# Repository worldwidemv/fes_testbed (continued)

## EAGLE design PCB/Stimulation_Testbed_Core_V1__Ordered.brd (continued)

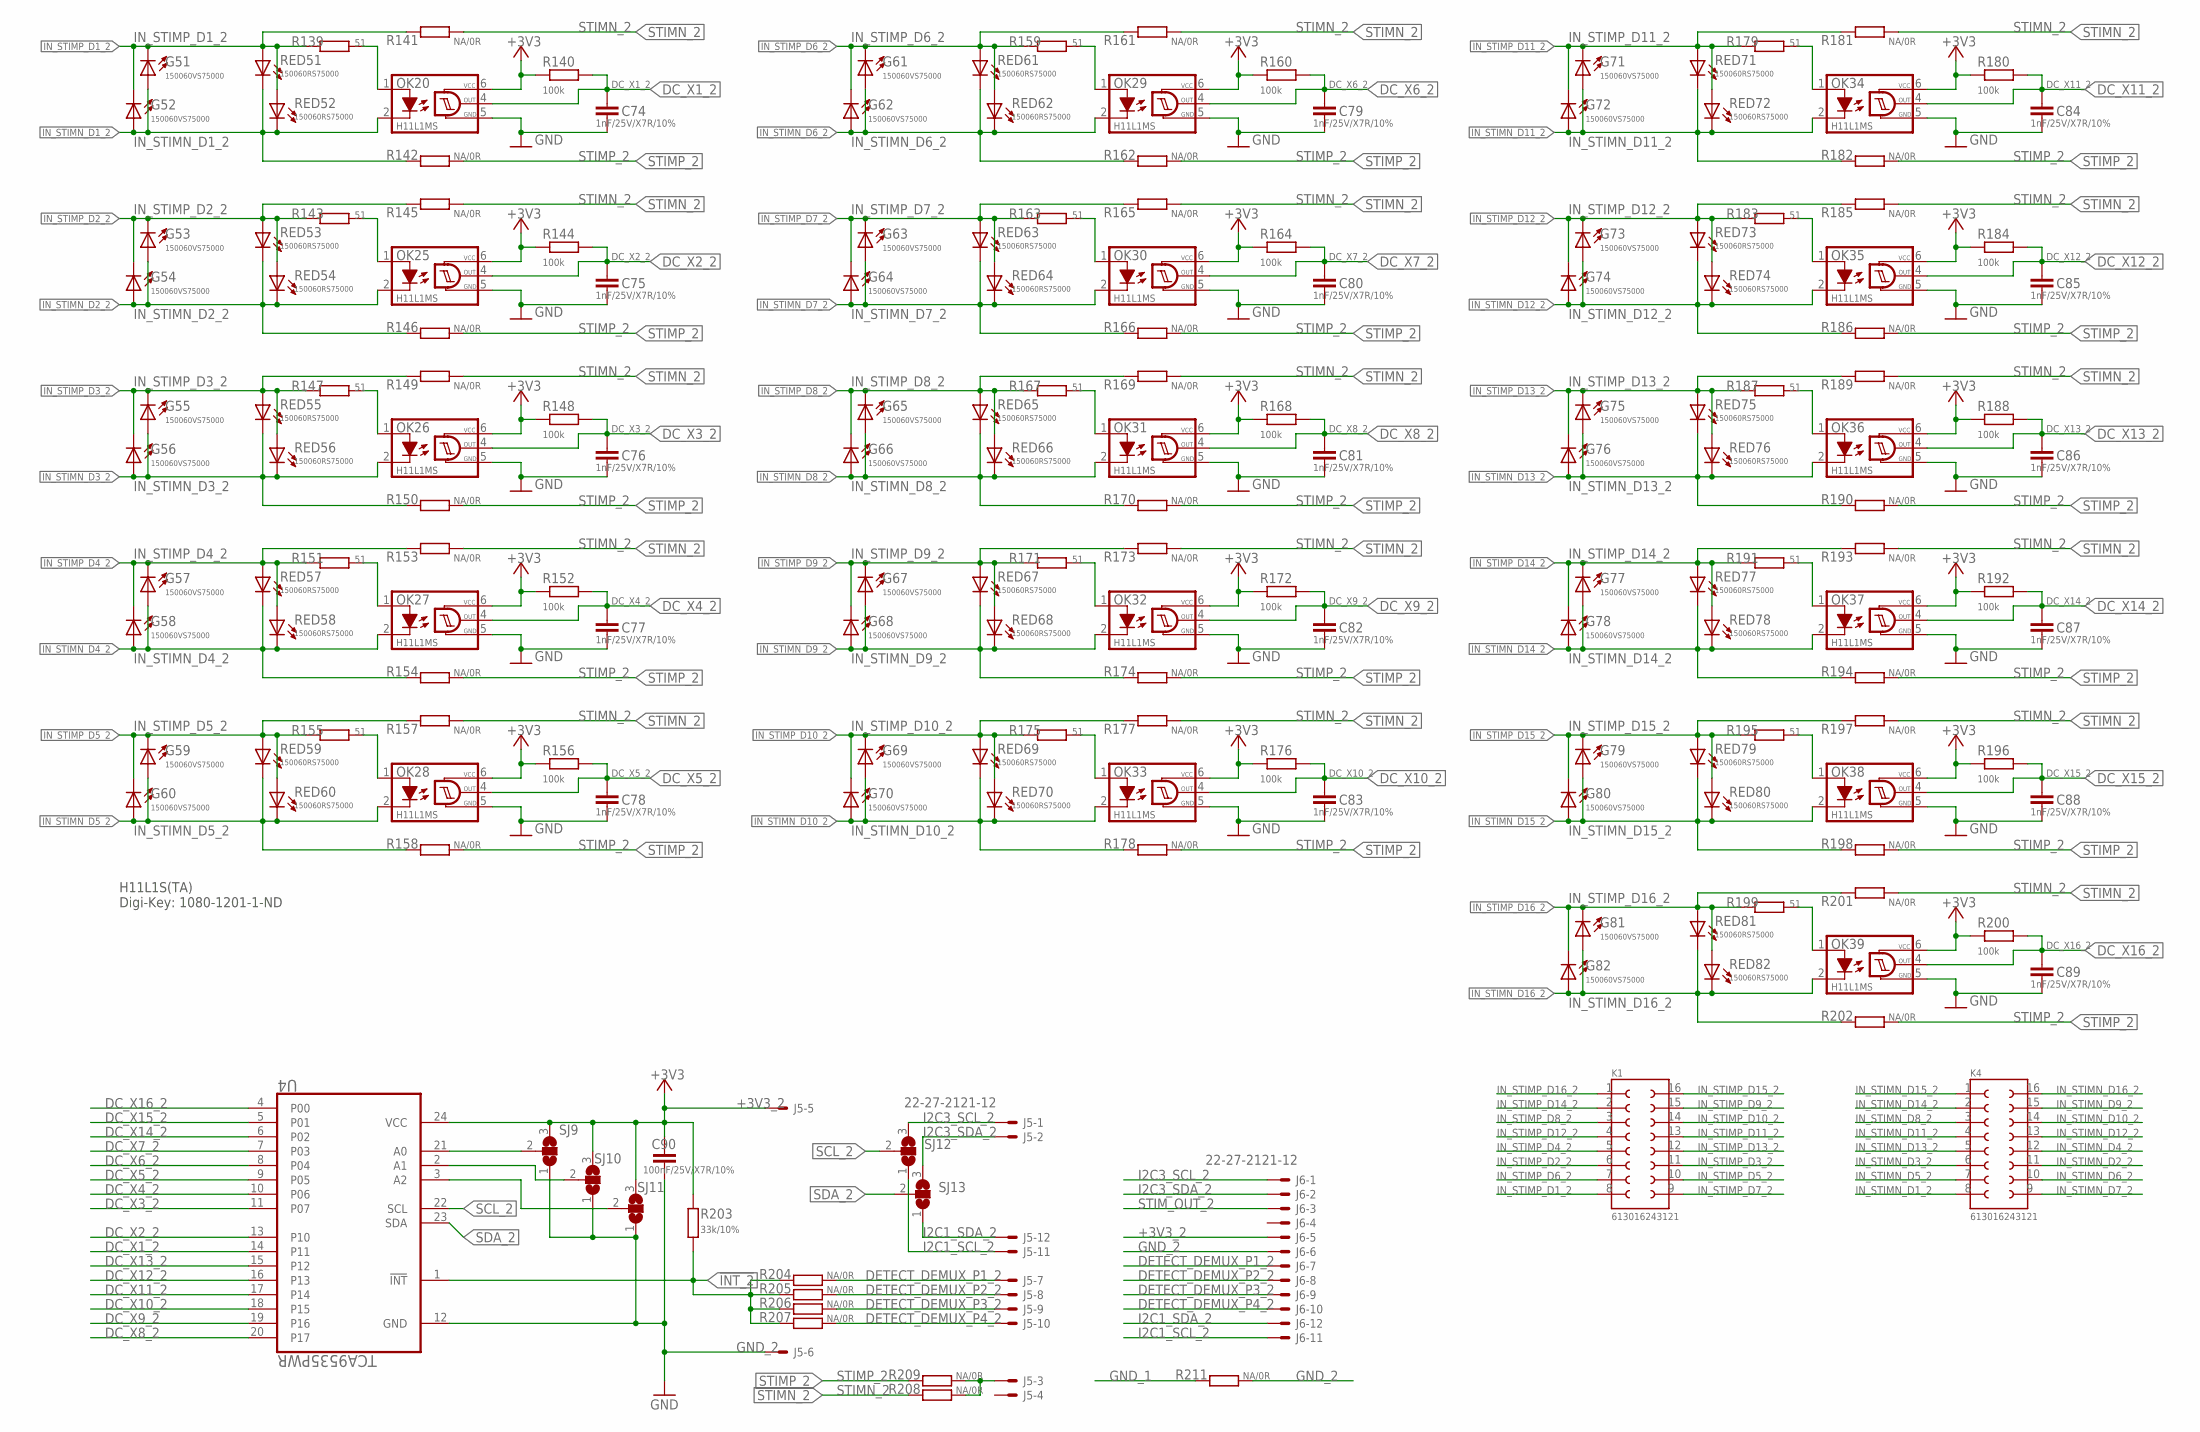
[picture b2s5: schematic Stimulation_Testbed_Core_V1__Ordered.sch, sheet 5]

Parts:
C74, C75, C76, C77, C78, C79, C80, C81, C82, C83, C84, C85, C86, C87, C88, C89: 1nF/25V/X7R/10%; C0603
C90: 100nF/25V/X7R/10%; C0603K
G51, G52, G53, G54, G55, G56, G57, G58, G59, G60, G61, G62, G63, G64, G65, G66, G67, G68, G69, G70, G71, G72, G73, G74, G75, G76, G77, G78, G79, G80, G81, G82: 150060VS75000; CHIPLED_0603
J5, J6: 22-27-2121-12; 6410-12
K1, K4: 613016243121
OK20, OK25, OK26, OK27, OK28, OK29, OK30, OK31, OK32, OK33, OK34, OK35, OK36, OK37, OK38, OK39: H11L1MS; DIL6-SMD
R139, R143, R147, R151, R155, R159, R163, R167, R171, R175, R179, R183, R187, R191, R195, R199: 51; R0603
R140, R144, R148, R152, R156, R160, R164, R168, R172, R176, R180, R184, R188, R192, R196, R200: 100k; R0603
R141, R142, R145, R146, R149, R150, R153, R154, R157, R158, R161, R162, R165, R166, R169, R170, R173, R174, R177, R178, R181, R182, R185, R186, R189, R190, R193, R194, R197, R198, R201, R202, R204, R205, R206, R207, R208, R209: NA/0R; R0603
R203: 33k/10%; R0603
R211: NA/0R; R6332
RED51, RED52, RED53, RED54, RED55, RED56, RED57, RED58, RED59, RED60, RED61, RED62, RED63, RED64, RED65, RED66, RED67, RED68, RED69, RED70, RED71, RED72, RED73, RED74, RED75, RED76, RED77, RED78, RED79, RED80, RED81, RED82: 150060RS75000; CHIP-LED0603
SJ9, SJ10, SJ11, SJ12, SJ13: SJ2W; SJ_2
U4: TCA9535PWR; SOP65P640X120-24N

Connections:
!INT_2: R203.1, R204.2, R205.2, R206.2, R207.2, U4.1 (!INT)
+3V3_2: C90.1, J5.5, J6.5, OK20.6 (VCC), OK25.6 (VCC), OK26.6 (VCC), OK27.6 (VCC), OK28.6 (VCC), OK29.6 (VCC), OK30.6 (VCC), OK31.6 (VCC), OK32.6 (VCC), OK33.6 (VCC), OK34.6 (VCC), OK35.6 (VCC), OK36.6 (VCC), OK37.6 (VCC), OK38.6 (VCC), OK39.6 (VCC), R140.1, R144.1, R148.1, R152.1, R156.1, R160.1, R164.1, R168.1, R172.1, R176.1, R180.1, R184.1, R188.1, R192.1, R196.1, R200.1, R203.2, SJ9.3, SJ10.3, SJ11.3, U4.24 (VCC)
DC_X1_2: C74.1, OK20.4 (OUT), R140.2, U4.14 (P11)
DC_X2_2: C75.1, OK25.4 (OUT), R144.2, U4.13 (P10)
DC_X3_2: C76.1, OK26.4 (OUT), R148.2, U4.11 (P07)
DC_X4_2: C77.1, OK27.4 (OUT), R152.2, U4.10 (P06)
DC_X5_2: C78.1, OK28.4 (OUT), R156.2, U4.9 (P05)
DC_X6_2: C79.1, OK29.4 (OUT), R160.2, U4.8 (P04)
DC_X7_2: C80.1, OK30.4 (OUT), R164.2, U4.7 (P03)
DC_X8_2: C81.1, OK31.4 (OUT), R168.2, U4.20 (P17)
DC_X9_2: C82.1, OK32.4 (OUT), R172.2, U4.19 (P16)
DC_X10_2: C83.1, OK33.4 (OUT), R176.2, U4.18 (P15)
DC_X11_2: C84.1, OK34.4 (OUT), R180.2, U4.17 (P14)
DC_X12_2: C85.1, OK35.4 (OUT), R184.2, U4.16 (P13)
DC_X13_2: C86.1, OK36.4 (OUT), R188.2, U4.15 (P12)
DC_X14_2: C87.1, OK37.4 (OUT), R192.2, U4.6 (P02)
DC_X15_2: C88.1, OK38.4 (OUT), R196.2, U4.5 (P01)
DC_X16_2: C89.1, OK39.4 (OUT), R200.2, U4.4 (P00)
DETECT_DEMUX_P1_2: J5.7, J6.7, R204.1
DETECT_DEMUX_P2_2: J5.8, J6.8, R205.1
DETECT_DEMUX_P3_2: J5.9, J6.9, R206.1
DETECT_DEMUX_P4_2: J5.10, J6.10, R207.1
GND_1: R211.2; also elsewhere on the board
GND_2: C74.2, C75.2, C76.2, C77.2, C78.2, C79.2, C80.2, C81.2, C82.2, C83.2, C84.2, C85.2, C86.2, C87.2, C88.2, C89.2, C90.2, J5.6, J6.6, OK20.5 (GND), OK25.5 (GND), OK26.5 (GND), OK27.5 (GND), OK28.5 (GND), OK29.5 (GND), OK30.5 (GND), OK31.5 (GND), OK32.5 (GND), OK33.5 (GND), OK34.5 (GND), OK35.5 (GND), OK36.5 (GND), OK37.5 (GND), OK38.5 (GND), OK39.5 (GND), R211.1, SJ9.1, SJ10.1, SJ11.1, U4.12 (GND)
I2C1_SCL_2: J5.11, J6.11, SJ12.1
I2C1_SDA_2: J5.12, J6.12, SJ13.1
I2C3_SCL_2: J5.1, J6.1, SJ12.3
I2C3_SDA_2: J5.2, J6.2, SJ13.3
IN_STIMN_D1_2: G51.A, G52.A, K4.8, OK20.2 (C), R142.2, RED51.C, RED52.C
IN_STIMN_D2_2: G53.A, G54.A, K4.11, OK25.2 (C), R146.2, RED53.C, RED54.C
IN_STIMN_D3_2: G55.A, G56.A, K4.6, OK26.2 (C), R150.2, RED55.C, RED56.C
IN_STIMN_D4_2: G57.A, G58.A, K4.12, OK27.2 (C), R154.2, RED57.C, RED58.C
IN_STIMN_D5_2: G59.A, G60.A, K4.7, OK28.2 (C), R158.2, RED59.C, RED60.C
IN_STIMN_D6_2: G61.A, G62.A, K4.10, OK29.2 (C), R162.2, RED61.C, RED62.C
IN_STIMN_D7_2: G63.A, G64.A, K4.9, OK30.2 (C), R166.2, RED63.C, RED64.C
IN_STIMN_D8_2: G65.A, G66.A, K4.3, OK31.2 (C), R170.2, RED65.C, RED66.C
IN_STIMN_D9_2: G67.A, G68.A, K4.15, OK32.2 (C), R174.2, RED67.C, RED68.C
IN_STIMN_D10_2: G69.A, G70.A, K4.14, OK33.2 (C), R178.2, RED69.C, RED70.C
IN_STIMN_D11_2: G71.A, G72.A, K4.4, OK34.2 (C), R182.2, RED71.C, RED72.C
IN_STIMN_D12_2: G73.A, G74.A, K4.13, OK35.2 (C), R186.2, RED73.C, RED74.C
IN_STIMN_D13_2: G75.A, G76.A, K4.5, OK36.2 (C), R190.2, RED75.C, RED76.C
IN_STIMN_D14_2: G77.A, G78.A, K4.2, OK37.2 (C), R194.2, RED77.C, RED78.C
IN_STIMN_D15_2: G79.A, G80.A, K4.1, OK38.2 (C), R198.2, RED79.C, RED80.C
IN_STIMN_D16_2: G81.A, G82.A, K4.16, OK39.2 (C), R202.2, RED81.C, RED82.C
IN_STIMP_D1_2: G51.C, G52.C, K1.8, R139.2, R141.2, RED51.A, RED52.A
IN_STIMP_D2_2: G53.C, G54.C, K1.6, R143.2, R145.2, RED53.A, RED54.A
IN_STIMP_D3_2: G55.C, G56.C, K1.11, R147.2, R149.2, RED55.A, RED56.A
IN_STIMP_D4_2: G57.C, G58.C, K1.5, R151.2, R153.2, RED57.A, RED58.A
IN_STIMP_D5_2: G59.C, G60.C, K1.10, R155.2, R157.2, RED59.A, RED60.A
IN_STIMP_D6_2: G61.C, G62.C, K1.7, R159.2, R161.2, RED61.A, RED62.A
IN_STIMP_D7_2: G63.C, G64.C, K1.9, R163.2, R165.2, RED63.A, RED64.A
IN_STIMP_D8_2: G65.C, G66.C, K1.3, R167.2, R169.2, RED65.A, RED66.A
IN_STIMP_D9_2: G67.C, G68.C, K1.15, R171.2, R173.2, RED67.A, RED68.A
IN_STIMP_D10_2: G69.C, G70.C, K1.14, R175.2, R177.2, RED69.A, RED70.A
IN_STIMP_D11_2: G71.C, G72.C, K1.13, R179.2, R181.2, RED71.A, RED72.A
IN_STIMP_D12_2: G73.C, G74.C, K1.4, R183.2, R185.2, RED73.A, RED74.A
IN_STIMP_D13_2: G75.C, G76.C, K1.12, R187.2, R189.2, RED75.A, RED76.A
IN_STIMP_D14_2: G77.C, G78.C, K1.2, R191.2, R193.2, RED77.A, RED78.A
IN_STIMP_D15_2: G79.C, G80.C, K1.16, R195.2, R197.2, RED79.A, RED80.A
IN_STIMP_D16_2: G81.C, G82.C, K1.1, R199.2, R201.2, RED81.A, RED82.A
unnamed: OK25.1 (A), R143.1
unnamed: OK20.1 (A), R139.1
unnamed: OK26.1 (A), R147.1
unnamed: OK27.1 (A), R151.1
unnamed: OK28.1 (A), R155.1
unnamed: OK29.1 (A), R159.1
unnamed: OK30.1 (A), R163.1
unnamed: OK31.1 (A), R167.1
unnamed: OK33.1 (A), R175.1
unnamed: OK32.1 (A), R171.1
unnamed: OK34.1 (A), R179.1
unnamed: OK35.1 (A), R183.1
unnamed: OK36.1 (A), R187.1
unnamed: OK37.1 (A), R191.1
unnamed: OK38.1 (A), R195.1
unnamed: OK39.1 (A), R199.1
unnamed: SJ9.2, U4.21 (A0)
unnamed: SJ10.2, U4.2 (A1)
unnamed: SJ11.2, U4.3 (A2)
SCL_2: SJ12.2, U4.22 (SCL)
SDA_2: SJ13.2, U4.23 (SDA)
STIMN_2: R141.1, R145.1, R149.1, R153.1, R157.1, R161.1, R165.1, R169.1, R173.1, R177.1, R181.1, R185.1, R189.1, R193.1, R197.1, R201.1, R208.2
STIMP_2: R142.1, R146.1, R150.1, R154.1, R158.1, R162.1, R166.1, R170.1, R174.1, R178.1, R182.1, R186.1, R190.1, R194.1, R198.1, R202.1, R209.2
STIM_OUT_2: J5.3, J6.3, R208.1, R209.1

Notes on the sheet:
H11L1S(TA) Digi-Key: 1080-1201-1-ND

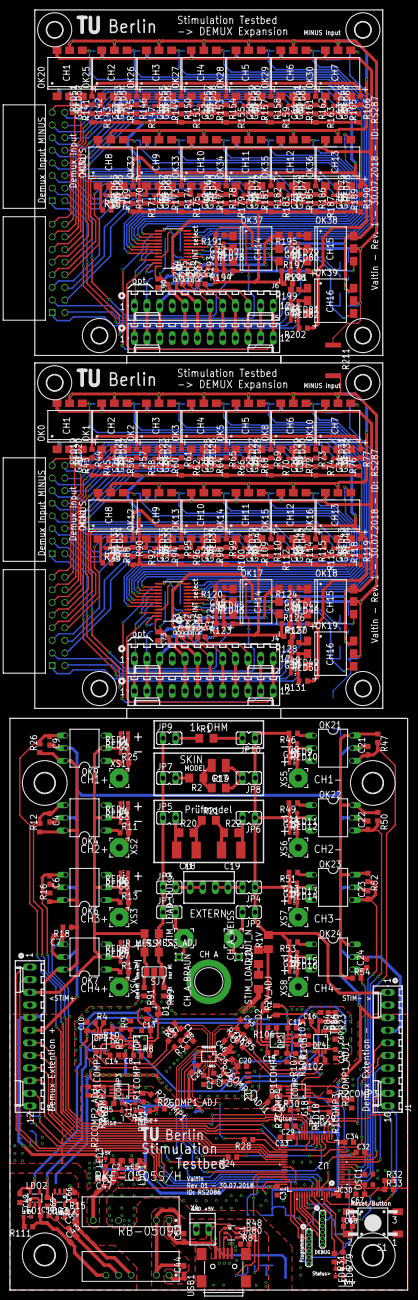
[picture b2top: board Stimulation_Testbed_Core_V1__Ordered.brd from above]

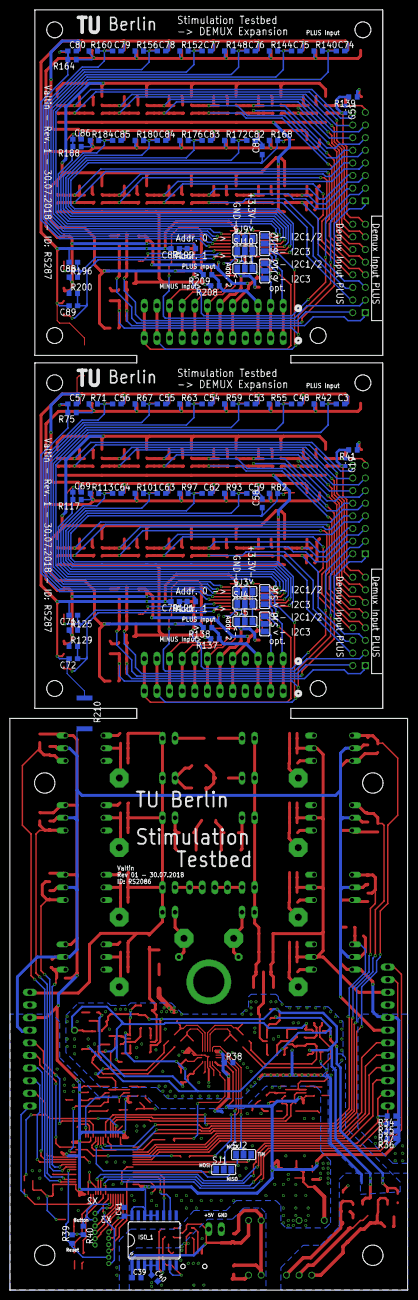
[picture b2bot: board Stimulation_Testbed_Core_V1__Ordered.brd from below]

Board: 2 copper layers, 80.0 x 257.5 mm, 613 parts (96 on the bottom side), 311 nets.

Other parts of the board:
U$1, U$2, U$3, U$4: 4,1
U$5, U$6, U$7, U$8, U$9, U$10, U$11, U$12: 3,2

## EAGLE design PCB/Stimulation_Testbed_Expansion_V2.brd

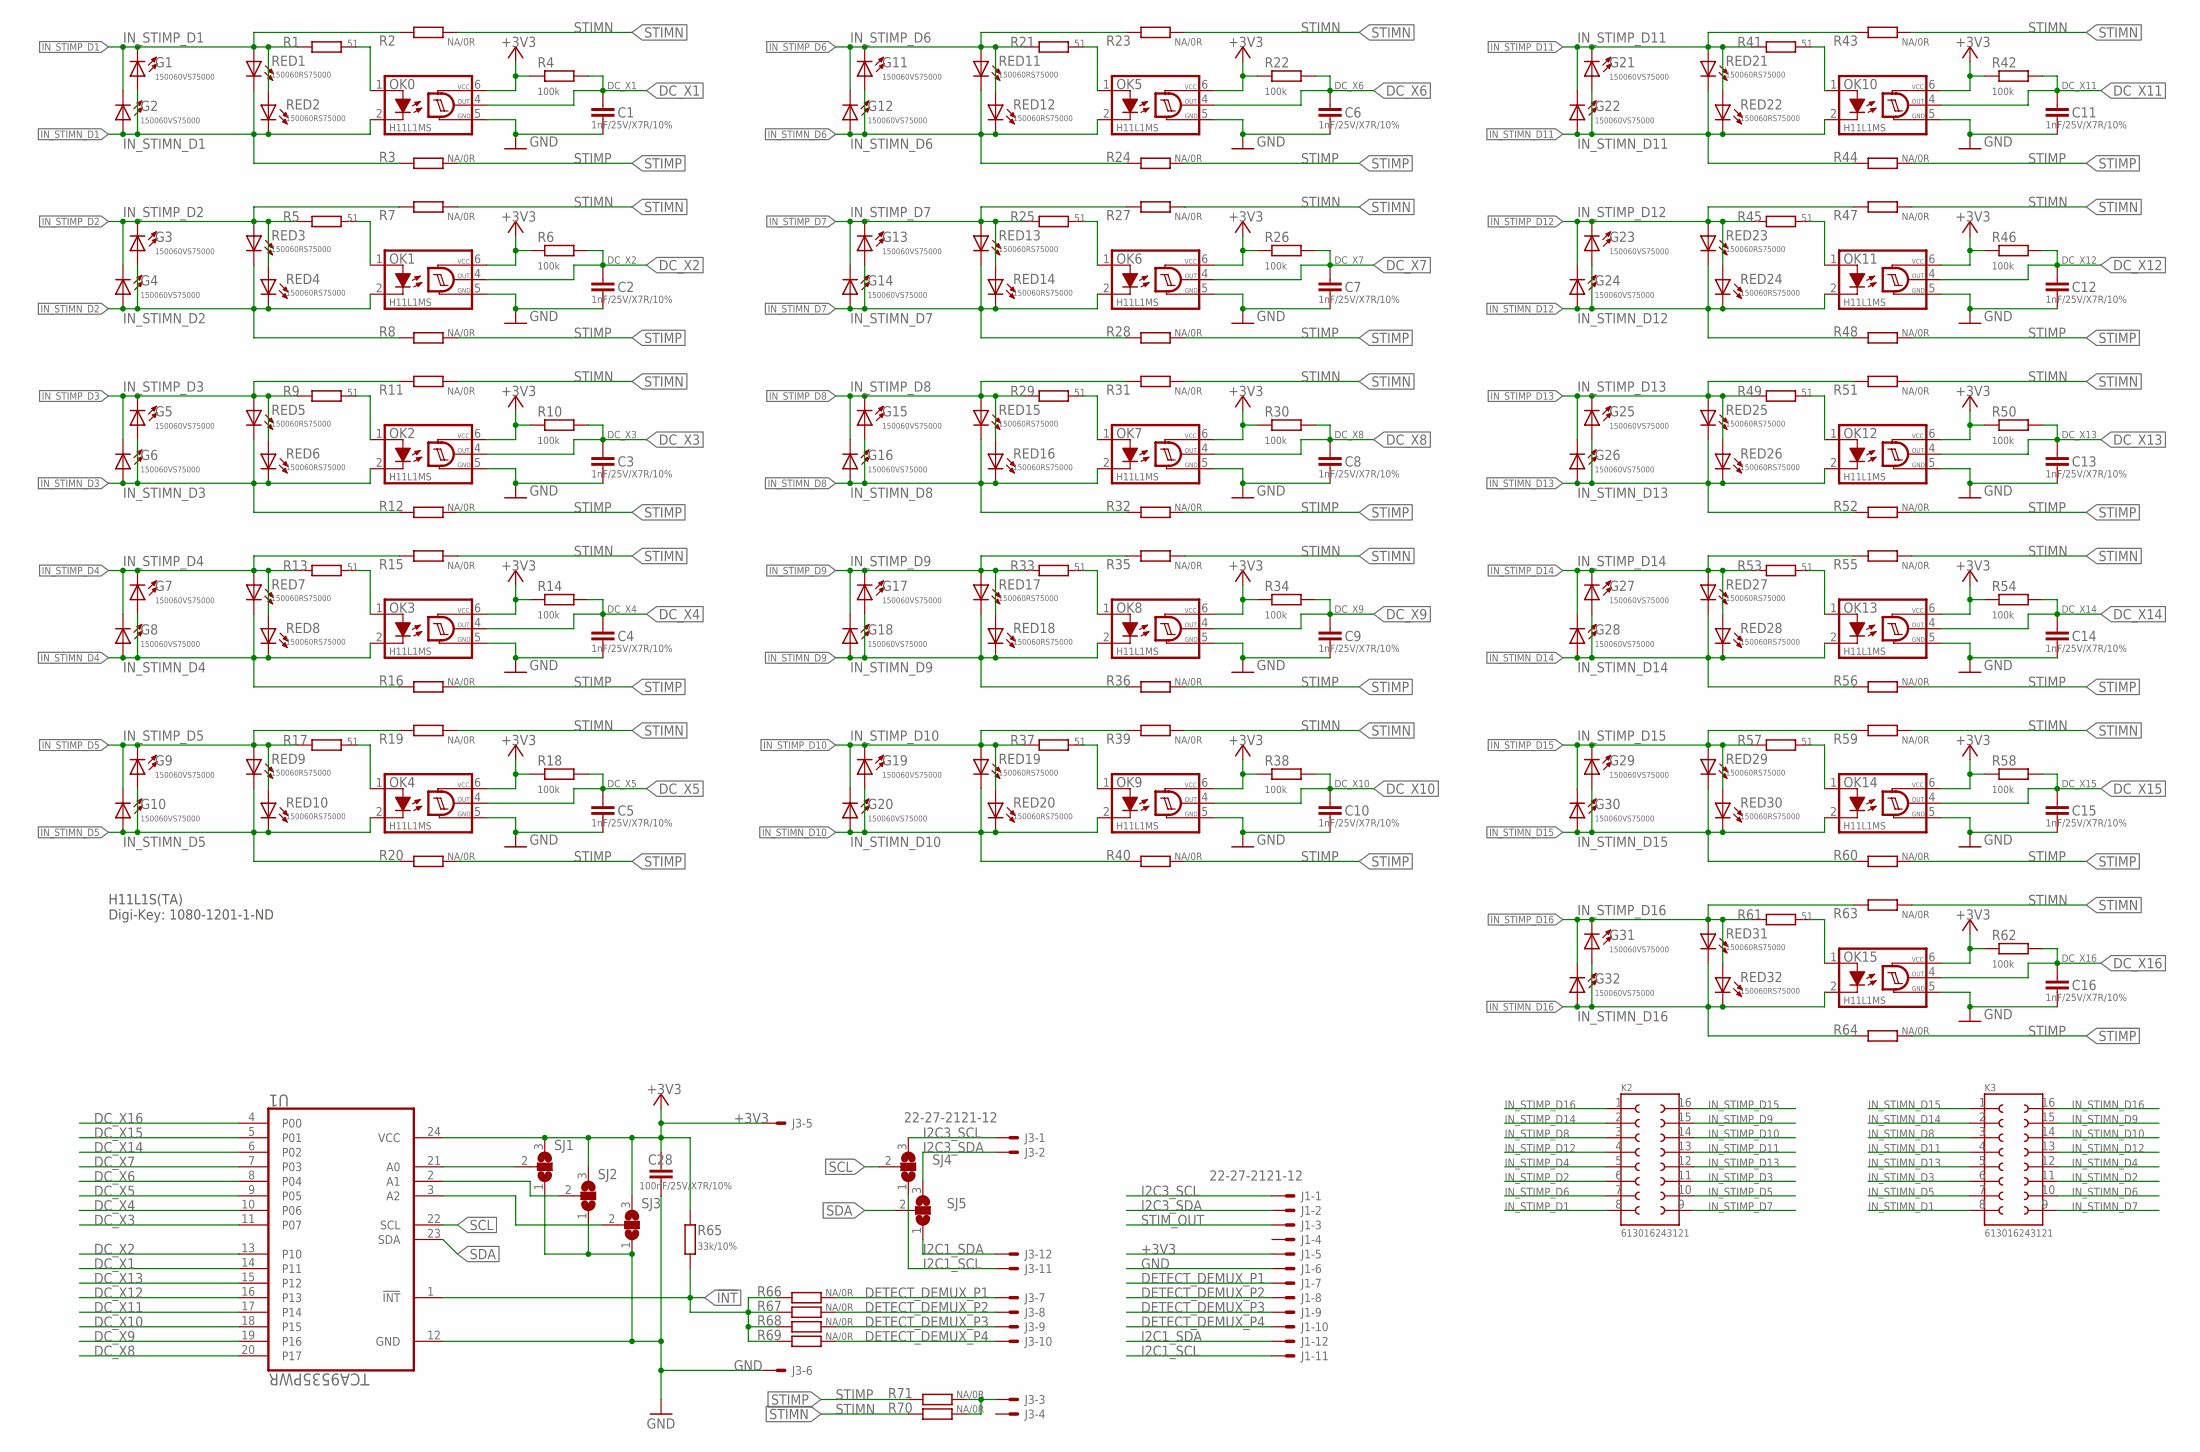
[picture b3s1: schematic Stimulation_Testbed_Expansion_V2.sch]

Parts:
C1, C2, C3, C4, C5, C6, C7, C8, C9, C10, C11, C12, C13, C14, C15, C16: 1nF/25V/X7R/10%; C0603
C28: 100nF/25V/X7R/10%; C0603K
G1, G2, G3, G4, G5, G6, G7, G8, G9, G10, G11, G12, G13, G14, G15, G16, G17, G18, G19, G20, G21, G22, G23, G24, G25, G26, G27, G28, G29, G30, G31, G32: 150060VS75000; CHIPLED_0603
J1, J3: 22-27-2121-12; 6410-12
K2, K3: 613016243121
OK0, OK1, OK2, OK3, OK4, OK5, OK6, OK7, OK8, OK9, OK10, OK11, OK12, OK13, OK14, OK15: H11L1MS; DIL6-SMD
R1, R5, R9, R13, R17, R21, R25, R29, R33, R37, R41, R45, R49, R53, R57, R61: 51; R0603
R2, R3, R7, R8, R11, R12, R15, R16, R19, R20, R23, R24, R27, R28, R31, R32, R35, R36, R39, R40, R43, R44, R47, R48, R51, R52, R55, R56, R59, R60, R63, R64, R66, R67, R68, R69, R70, R71: NA/0R; R0603
R4, R6, R10, R14, R18, R22, R26, R30, R34, R38, R42, R46, R50, R54, R58, R62: 100k; R0603
R65: 33k/10%; R0603
RED1, RED2, RED3, RED4, RED5, RED6, RED7, RED8, RED9, RED10, RED11, RED12, RED13, RED14, RED15, RED16, RED17, RED18, RED19, RED20, RED21, RED22, RED23, RED24, RED25, RED26, RED27, RED28, RED29, RED30, RED31, RED32: 150060RS75000; CHIP-LED0603
SJ1, SJ2, SJ3, SJ4, SJ5: SJ2W; SJ_2
U1: TCA9535PWR; SOP65P640X120-24N

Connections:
!INT: R65.1, R66.2, R67.2, R68.2, R69.2, U1.1 (!INT)
+3V3: C28.1, J1.5, J3.5, OK0.6 (VCC), OK1.6 (VCC), OK2.6 (VCC), OK3.6 (VCC), OK4.6 (VCC), OK5.6 (VCC), OK6.6 (VCC), OK7.6 (VCC), OK8.6 (VCC), OK9.6 (VCC), OK10.6 (VCC), OK11.6 (VCC), OK12.6 (VCC), OK13.6 (VCC), OK14.6 (VCC), OK15.6 (VCC), R4.1, R6.1, R10.1, R14.1, R18.1, R22.1, R26.1, R30.1, R34.1, R38.1, R42.1, R46.1, R50.1, R54.1, R58.1, R62.1, R65.2, SJ1.3, SJ2.3, SJ3.3, U1.24 (VCC)
DC_X1: C1.1, OK0.4 (OUT), R4.2, U1.14 (P11)
DC_X2: C2.1, OK1.4 (OUT), R6.2, U1.13 (P10)
DC_X3: C3.1, OK2.4 (OUT), R10.2, U1.11 (P07)
DC_X4: C4.1, OK3.4 (OUT), R14.2, U1.10 (P06)
DC_X5: C5.1, OK4.4 (OUT), R18.2, U1.9 (P05)
DC_X6: C6.1, OK5.4 (OUT), R22.2, U1.8 (P04)
DC_X7: C7.1, OK6.4 (OUT), R26.2, U1.7 (P03)
DC_X8: C8.1, OK7.4 (OUT), R30.2, U1.20 (P17)
DC_X9: C9.1, OK8.4 (OUT), R34.2, U1.19 (P16)
DC_X10: C10.1, OK9.4 (OUT), R38.2, U1.18 (P15)
DC_X11: C11.1, OK10.4 (OUT), R42.2, U1.17 (P14)
DC_X12: C12.1, OK11.4 (OUT), R46.2, U1.16 (P13)
DC_X13: C13.1, OK12.4 (OUT), R50.2, U1.15 (P12)
DC_X14: C14.1, OK13.4 (OUT), R54.2, U1.6 (P02)
DC_X15: C15.1, OK14.4 (OUT), R58.2, U1.5 (P01)
DC_X16: C16.1, OK15.4 (OUT), R62.2, U1.4 (P00)
DETECT_DEMUX_P1: J1.7, J3.7, R66.1
DETECT_DEMUX_P2: J1.8, J3.8, R67.1
DETECT_DEMUX_P3: J1.9, J3.9, R68.1
DETECT_DEMUX_P4: J1.10, J3.10, R69.1
GND: C1.2, C2.2, C3.2, C4.2, C5.2, C6.2, C7.2, C8.2, C9.2, C10.2, C11.2, C12.2, C13.2, C14.2, C15.2, C16.2, C28.2, J1.6, J3.6, OK0.5 (GND), OK1.5 (GND), OK2.5 (GND), OK3.5 (GND), OK4.5 (GND), OK5.5 (GND), OK6.5 (GND), OK7.5 (GND), OK8.5 (GND), OK9.5 (GND), OK10.5 (GND), OK11.5 (GND), OK12.5 (GND), OK13.5 (GND), OK14.5 (GND), OK15.5 (GND), SJ1.1, SJ2.1, SJ3.1, U1.12 (GND)
I2C1_SCL: J1.11, J3.11, SJ4.1
I2C1_SDA: J1.12, J3.12, SJ5.1
I2C3_SCL: J1.1, J3.1, SJ4.3
I2C3_SDA: J1.2, J3.2, SJ5.3
IN_STIMN_D1: G1.A, G2.A, K3.8, OK0.2 (C), R3.2, RED1.C, RED2.C
IN_STIMN_D2: G3.A, G4.A, K3.11, OK1.2 (C), R8.2, RED3.C, RED4.C
IN_STIMN_D3: G5.A, G6.A, K3.6, OK2.2 (C), R12.2, RED5.C, RED6.C
IN_STIMN_D4: G7.A, G8.A, K3.12, OK3.2 (C), R16.2, RED7.C, RED8.C
IN_STIMN_D5: G9.A, G10.A, K3.7, OK4.2 (C), R20.2, RED9.C, RED10.C
IN_STIMN_D6: G11.A, G12.A, K3.10, OK5.2 (C), R24.2, RED11.C, RED12.C
IN_STIMN_D7: G13.A, G14.A, K3.9, OK6.2 (C), R28.2, RED13.C, RED14.C
IN_STIMN_D8: G15.A, G16.A, K3.3, OK7.2 (C), R32.2, RED15.C, RED16.C
IN_STIMN_D9: G17.A, G18.A, K3.15, OK8.2 (C), R36.2, RED17.C, RED18.C
IN_STIMN_D10: G19.A, G20.A, K3.14, OK9.2 (C), R40.2, RED19.C, RED20.C
IN_STIMN_D11: G21.A, G22.A, K3.4, OK10.2 (C), R44.2, RED21.C, RED22.C
IN_STIMN_D12: G23.A, G24.A, K3.13, OK11.2 (C), R48.2, RED23.C, RED24.C
IN_STIMN_D13: G25.A, G26.A, K3.5, OK12.2 (C), R52.2, RED25.C, RED26.C
IN_STIMN_D14: G27.A, G28.A, K3.2, OK13.2 (C), R56.2, RED27.C, RED28.C
IN_STIMN_D15: G29.A, G30.A, K3.1, OK14.2 (C), R60.2, RED29.C, RED30.C
IN_STIMN_D16: G31.A, G32.A, K3.16, OK15.2 (C), R64.2, RED31.C, RED32.C
IN_STIMP_D1: G1.C, G2.C, K2.8, R1.2, R2.2, RED1.A, RED2.A
IN_STIMP_D2: G3.C, G4.C, K2.6, R5.2, R7.2, RED3.A, RED4.A
IN_STIMP_D3: G5.C, G6.C, K2.11, R9.2, R11.2, RED5.A, RED6.A
IN_STIMP_D4: G7.C, G8.C, K2.5, R13.2, R15.2, RED7.A, RED8.A
IN_STIMP_D5: G9.C, G10.C, K2.10, R17.2, R19.2, RED9.A, RED10.A
IN_STIMP_D6: G11.C, G12.C, K2.7, R21.2, R23.2, RED11.A, RED12.A
IN_STIMP_D7: G13.C, G14.C, K2.9, R25.2, R27.2, RED13.A, RED14.A
IN_STIMP_D8: G15.C, G16.C, K2.3, R29.2, R31.2, RED15.A, RED16.A
IN_STIMP_D9: G17.C, G18.C, K2.15, R33.2, R35.2, RED17.A, RED18.A
IN_STIMP_D10: G19.C, G20.C, K2.14, R37.2, R39.2, RED19.A, RED20.A
IN_STIMP_D11: G21.C, G22.C, K2.13, R41.2, R43.2, RED21.A, RED22.A
IN_STIMP_D12: G23.C, G24.C, K2.4, R45.2, R47.2, RED23.A, RED24.A
IN_STIMP_D13: G25.C, G26.C, K2.12, R49.2, R51.2, RED25.A, RED26.A
IN_STIMP_D14: G27.C, G28.C, K2.2, R53.2, R55.2, RED27.A, RED28.A
IN_STIMP_D15: G29.C, G30.C, K2.16, R57.2, R59.2, RED29.A, RED30.A
IN_STIMP_D16: G31.C, G32.C, K2.1, R61.2, R63.2, RED31.A, RED32.A
unnamed: OK1.1 (A), R5.1
unnamed: OK2.1 (A), R9.1
unnamed: OK3.1 (A), R13.1
unnamed: OK4.1 (A), R17.1
unnamed: OK5.1 (A), R21.1
unnamed: OK6.1 (A), R25.1
unnamed: OK7.1 (A), R29.1
unnamed: OK9.1 (A), R37.1
unnamed: OK8.1 (A), R33.1
unnamed: OK10.1 (A), R41.1
unnamed: OK11.1 (A), R45.1
unnamed: OK12.1 (A), R49.1
unnamed: OK13.1 (A), R53.1
unnamed: OK14.1 (A), R57.1
unnamed: OK15.1 (A), R61.1
unnamed: SJ1.2, U1.21 (A0)
unnamed: SJ2.2, U1.2 (A1)
unnamed: SJ3.2, U1.3 (A2)
unnamed: OK0.1 (A), R1.1
SCL: SJ4.2, U1.22 (SCL)
SDA: SJ5.2, U1.23 (SDA)
STIMN: R2.1, R7.1, R11.1, R15.1, R19.1, R23.1, R27.1, R31.1, R35.1, R39.1, R43.1, R47.1, R51.1, R55.1, R59.1, R63.1, R70.2
STIMP: R3.1, R8.1, R12.1, R16.1, R20.1, R24.1, R28.1, R32.1, R36.1, R40.1, R44.1, R48.1, R52.1, R56.1, R60.1, R64.1, R71.2
STIM_OUT: J1.3, J3.3, R70.1, R71.1

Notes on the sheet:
H11L1S(TA) Digi-Key: 1080-1201-1-ND

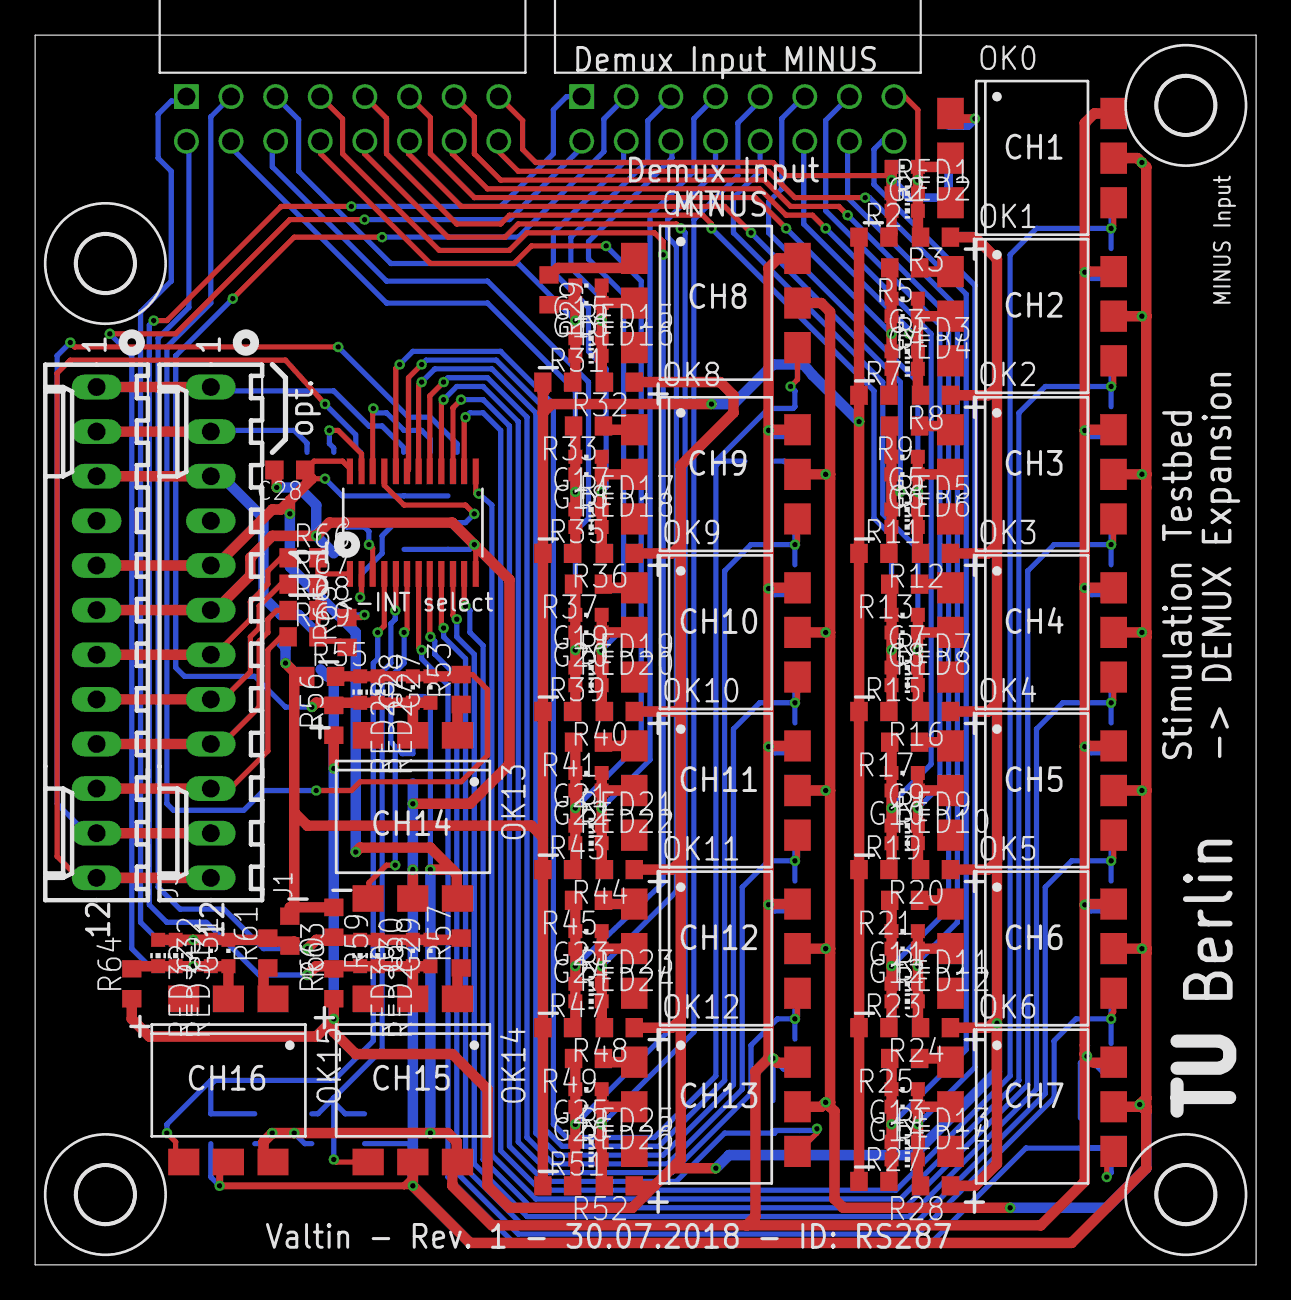
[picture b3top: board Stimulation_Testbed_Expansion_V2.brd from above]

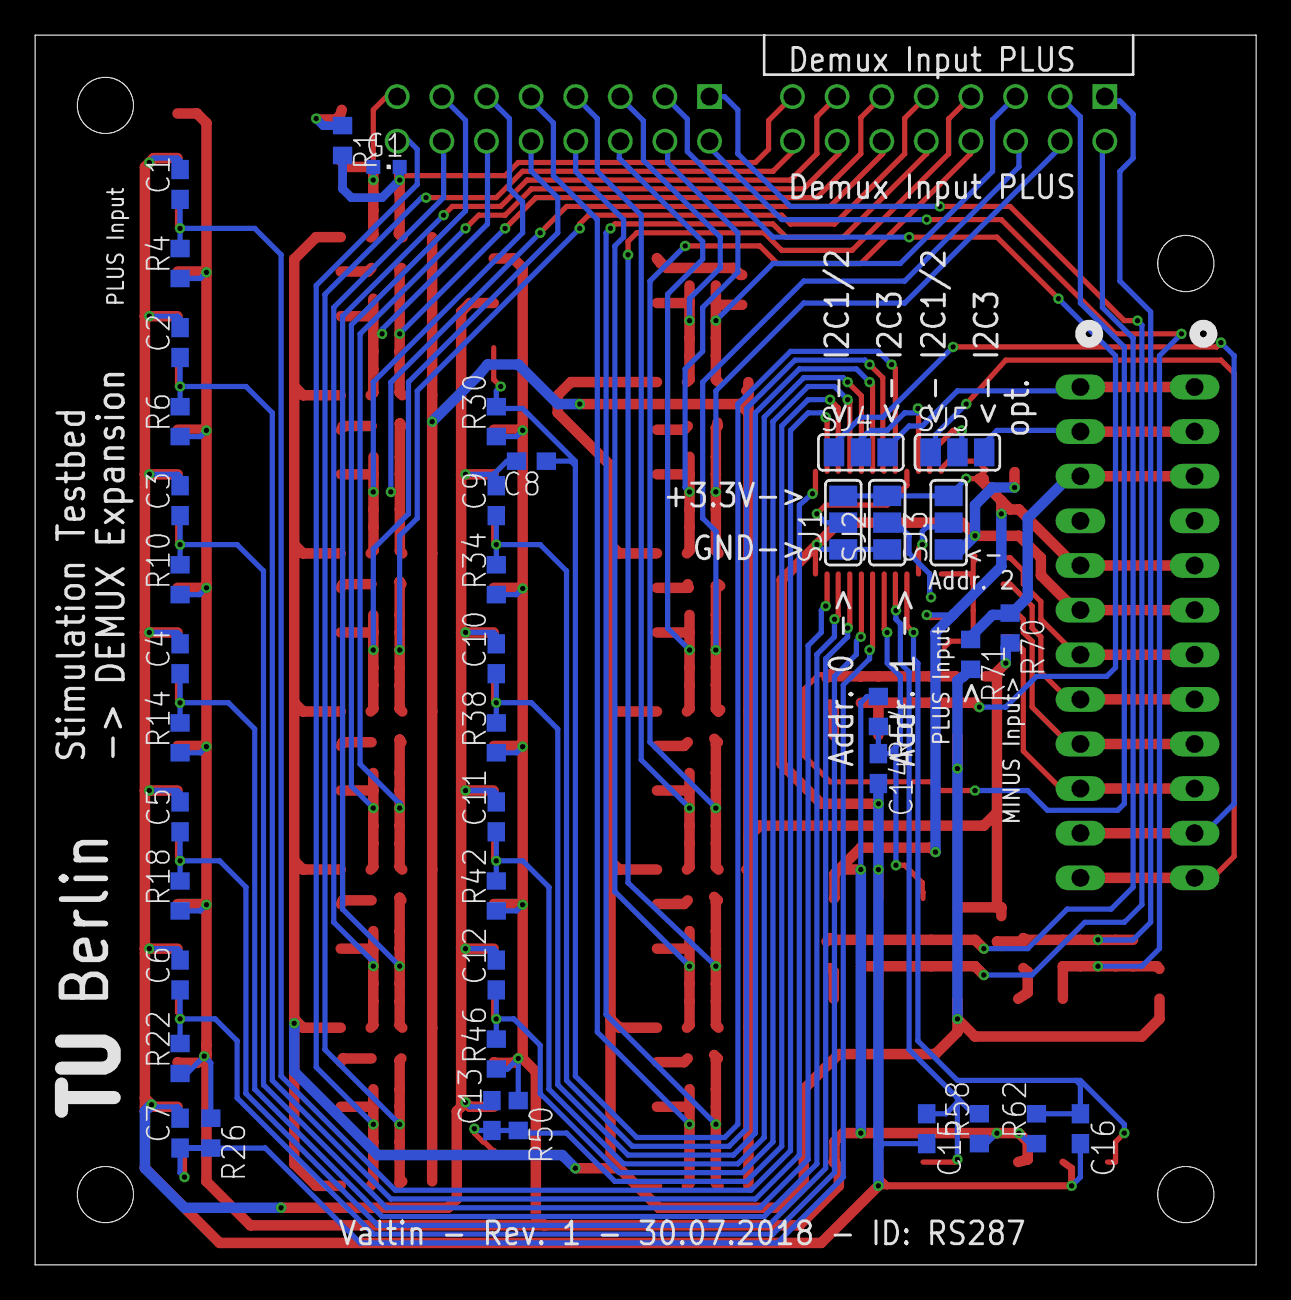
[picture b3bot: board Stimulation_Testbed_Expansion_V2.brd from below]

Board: 2 copper layers, 69.5 x 70.0 mm, 182 parts (41 on the bottom side), 83 nets.

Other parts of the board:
U$1, U$2, U$3, U$4: 3,2

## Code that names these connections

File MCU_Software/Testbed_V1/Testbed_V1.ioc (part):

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Mcu.Name=STM32F412R(E-G)Tx
Mcu.Package=LQFP64
Mcu.UserName=STM32F412RETx
PA0.GPIOParameters=GPIO_Label
PA0.GPIO_Label=Detect_V_P
PA0.Signal=GPXTI0
PA1.Mode=RX_Only_Simplex_Unidirect_Slave
PA1.Signal=SPI4_MOSI
PA10.Mode=RX_Only_Simplex_Unidirect_Slave
PA10.Signal=SPI5_MOSI
PA11.Mode=Device_Only
PA11.Signal=USB_OTG_FS_DM
PA12.Mode=Device_Only
PA12.Signal=USB_OTG_FS_DP
PA13.Mode=Trace_Asynchronous_SW
PA13.Signal=SYS_JTMS-SWDIO
PA14.Mode=Trace_Asynchronous_SW
PA14.Signal=SYS_JTCK-SWCLK
PA15.GPIOParameters=GPIO_Label
PA15.GPIO_Label=LED_Status
PA15.Signal=GPIO_Output
PA2.GPIOParameters=GPIO_Label
PA2.GPIO_Label=DD_N2
PA2.Signal=GPIO_Input
PA3.GPIOParameters=GPIO_Label
PA3.GPIO_Label=Detect_V_N
PA3.Signal=GPXTI3
PA4.GPIOParameters=GPIO_Label
PA4.GPIO_Label=DD_N1
PA4.Signal=GPIO_Input
PA5.Mode=Full_Duplex_Master
PA5.Signal=SPI1_SCK
PA6.Mode=Full_Duplex_Master
PA6.Signal=SPI1_MISO
PA7.GPIOParameters=GPIO_Label
PA7.GPIO_Label=SC_P2
PA7.Signal=GPIO_Input
PA8.Mode=I2C
PA8.Signal=I2C3_SCL
PB0.Mode=RX_Only_Simplex_Unidirect_Slave
PB0.Signal=SPI5_SCK
PB1.GPIOParameters=GPIO_Label
PB1.GPIO_Label=Detect_I_P
PB1.Signal=GPXTI1
PB10.Mode=I2C
PB10.Signal=I2C2_SCL
PB12.GPIOParameters=GPIO_Label
PB12.GPIO_Label=SC_P1
PB12.Signal=GPIO_Input
PB13.Mode=RX_Only_Simplex_Unidirect_Slave
PB13.Signal=SPI4_SCK
PB14.GPIOParameters=GPIO_Label
PB14.GPIO_Label=DD_P1
PB14.Signal=GPIO_Input
PB15.GPIOParameters=GPIO_Label
PB15.GPIO_Label=DD_P2
PB15.Signal=GPIO_Input
PB2.GPIOParameters=GPIO_Label
PB2.GPIO_Label=Detect_I_N
PB2.Signal=GPXTI2
PB3.Mode=Trace_Asynchronous_SW
PB3.Signal=SYS_JTDO-SWO
PB4.Mode=I2C
PB4.Signal=I2C3_SDA
PB5.Mode=Full_Duplex_Master
PB5.Signal=SPI1_MOSI
PB6.Mode=I2C
PB6.Signal=I2C1_SCL
PB7.Mode=I2C
PB7.Signal=I2C1_SDA
PB8.GPIOParameters=GPIO_Label
PB8.GPIO_Label=LED_Error
PB8.Signal=GPIO_Output
PB9.Mode=I2C
PB9.Signal=I2C2_SDA
PC0.GPIOParameters=GPIO_Label
PC0.GPIO_Label=SC_N3
PC0.Signal=GPIO_Input
PC1.GPIOParameters=GPIO_Label
PC1.GPIO_Label=SC_N4
PC1.Signal=GPIO_Input
PC10.Mode=Asynchronous
PC10.Signal=USART3_TX
PC11.Mode=Asynchronous
PC11.Signal=USART3_RX
PC12.GPIOParameters=GPIO_Label
PC12.GPIO_Label=D1
PC12.Signal=GPIO_Output
PC13.GPIOParameters=GPIO_Label
PC13.GPIO_Label=SC_N1
PC13.Signal=GPIO_Input
PC14-OSC32_IN.GPIOParameters=GPIO_Label
PC14-OSC32_IN.GPIO_Label=SC_N2
PC14-OSC32_IN.Signal=GPIO_Input
PC2.GPIOParameters=GPIO_Label
PC2.GPIO_Label=DD_N4
PC2.Signal=GPIO_Input
PC3.GPIOParameters=GPIO_Label
PC3.GPIO_Label=DD_N3
PC3.Signal=GPIO_Input
PC4.GPIOParameters=GPIO_Label
PC4.GPIO_Label=SC_P3
PC4.Signal=GPIO_Input
PC5.GPIOParameters=GPIO_Label
PC5.GPIO_Label=SC_P4
PC5.Signal=GPIO_Input
PC6.GPIOParameters=GPIO_Label
PC6.GPIO_Label=DD_P3
PC6.Signal=GPIO_Input
PC7.GPIOParameters=GPIO_Label
PC7.GPIO_Label=DD_P4
PC7.Signal=GPIO_Input
PC8.Signal=S_TIM8_CH3
PD2.GPIOParameters=GPIO_Label
PD2.GPIO_Label=D2
PD2.Signal=GPIO_Output
PH0\ -\ OSC_IN.Mode=HSE-External-Clock-Source
PH0\ -\ OSC_IN.Signal=RCC_OSC_IN
PH1\ -\ OSC_OUT.Mode=HSE-External-Clock-Source
PH1\ -\ OSC_OUT.Signal=RCC_OSC_OUT
RCC.HSE_VALUE=8000000
RCC.SYSCLKFreq_VALUE=100000000
RCC.SYSCLKSource=RCC_SYSCLKSOURCE_PLLCLK
board=Testbed_v1

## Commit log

2019-09-24 Initial Release
2019-09-24 Readme update
2019-09-24 System Overview figures added
